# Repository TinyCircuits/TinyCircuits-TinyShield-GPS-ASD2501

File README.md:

# TinyCircuits TinyShield GPS Board
# ASD2501 Rev4

The design files are located under design_files/ for the TinyCircuits ASD2501 Rev 4 PCB.  This is a TinyShield board that has a GPS module, local power supply, antenna and level shifters to receive GPS data.

Format is in Cadsoft Eagle format - Eagle version 6.2 was used for the original design.

For more infomation on this, check out the product page at TinyCircuits.com:  https://tinycircuits.com/collections/sensors/products/gps-tinyshield

#License:

Design by TinyCircuits.
All design files are released under the Creative Commons Attribution Share-Alike 3.0 License, see the following link for details: http://creativecommons.org/licenses/by-sa/3.0

All text above must be included in any redistribution or derived design

This project uses designs and concepts developed as part of the Arduino project and the LilyPad project.  The TinyCircuits design files themselves (schematics, PCB and libraries) are not directly derived from these works' design files and have been created new, however the concepts and basic architecture behind the TinyDuino and TinyLily products are derived and we thank the hard work of the organizations below for their contributions to open-source hardware:
  
Original Arduino Uno Design by Team Arduino

LilyPad Arduino Design by Leah Buechley and Sparkfun Electronics

Please support the open-source hardware community

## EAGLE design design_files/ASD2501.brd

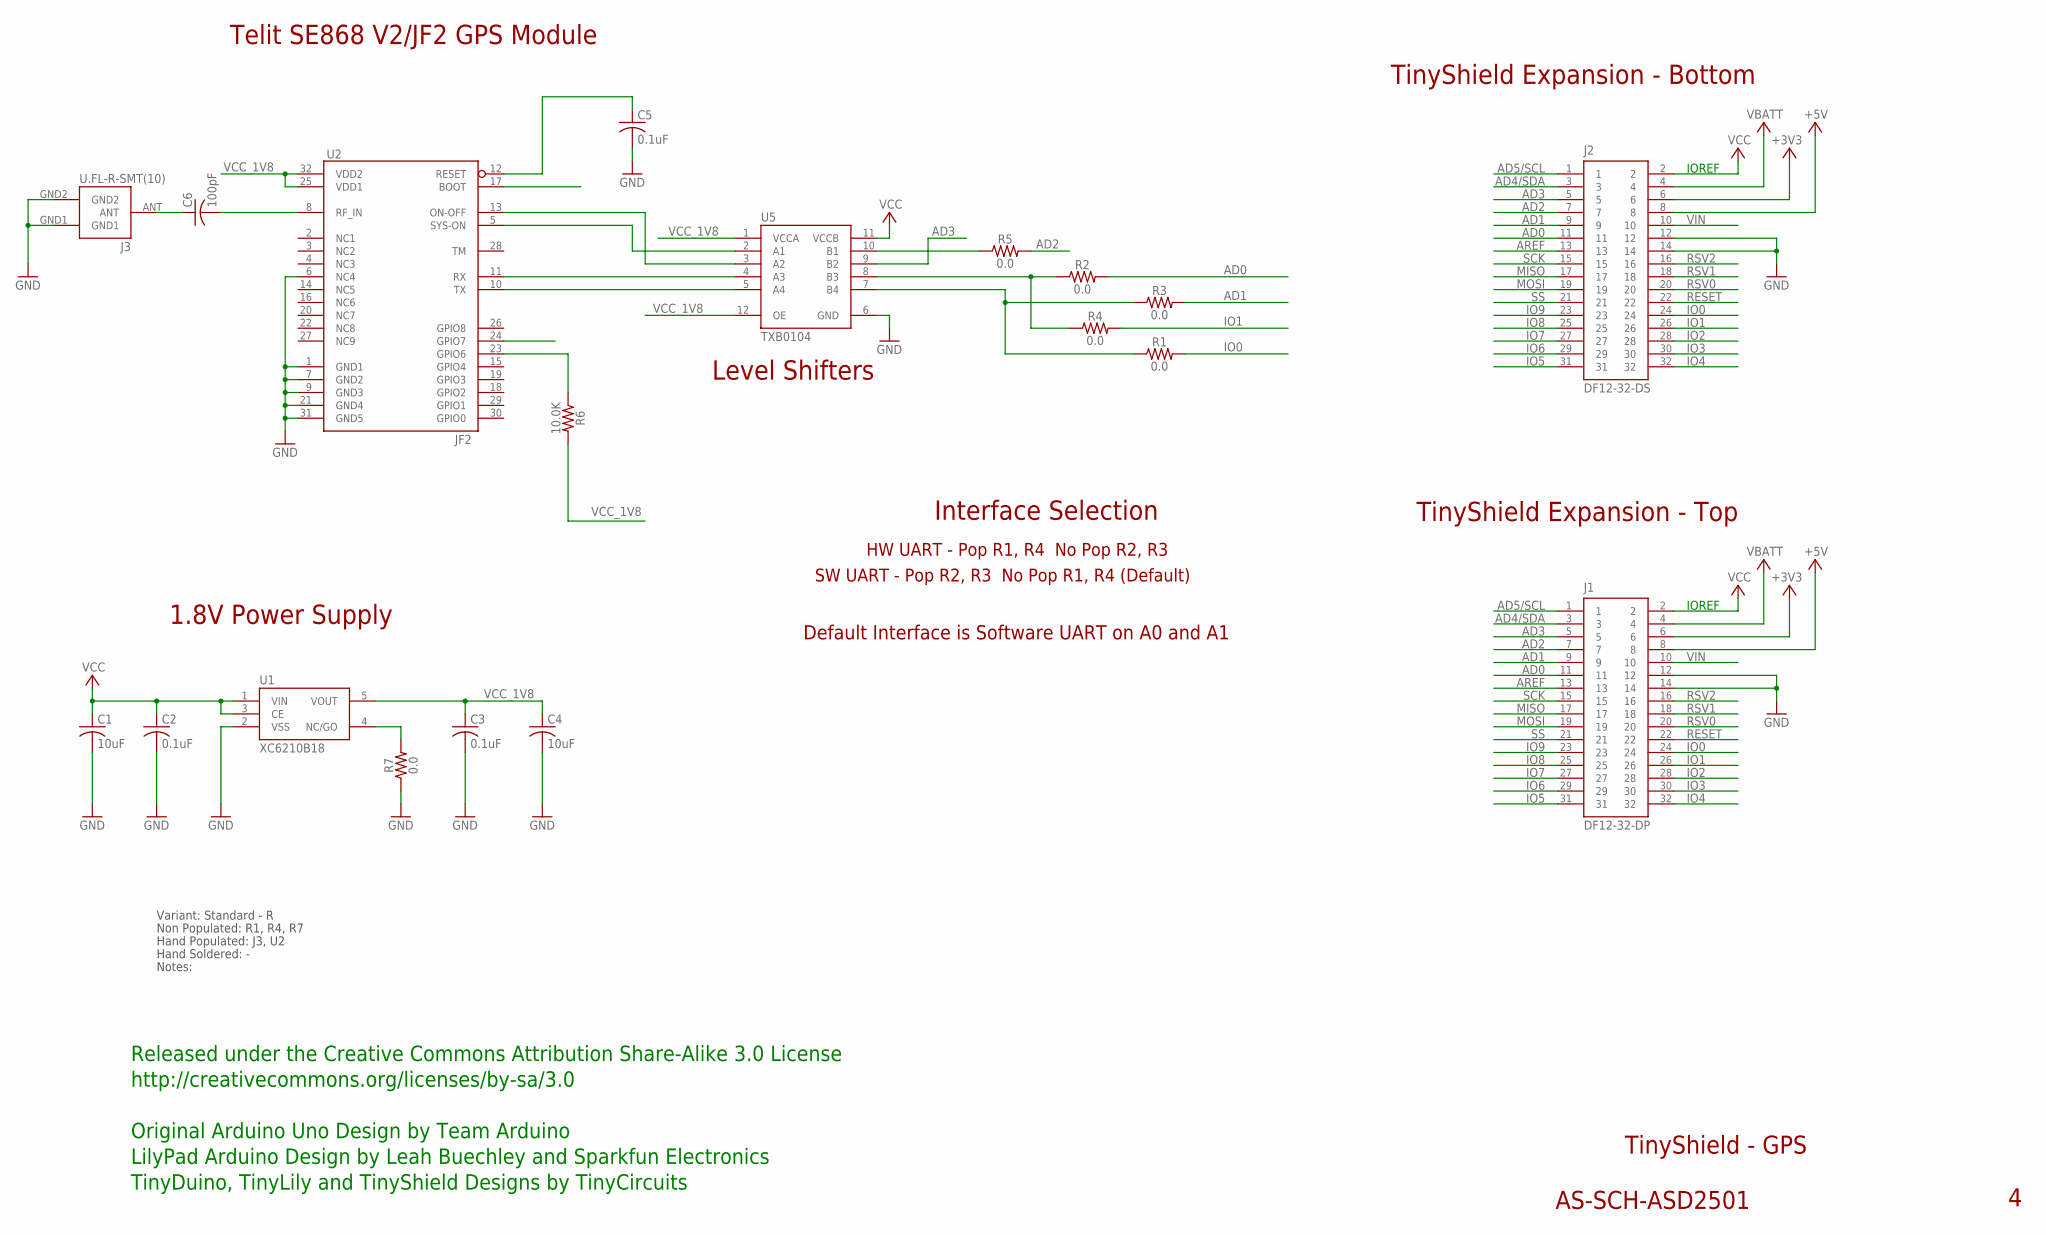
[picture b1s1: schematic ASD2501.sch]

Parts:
C1, C4: 10uF; C0805; PARTNO AS-ITM-00045
C2, C3, C5: 0.1uF; C0402; PARTNO AS-ITM-00008
C6: 100pF; 0402; PARTNO AS-ITM-00148
J1: DF12-32-DP; PARTNO AS-ITM-00015
J2: DF12-32-DS; PARTNO AS-ITM-00012
J3: U.FL-R-SMT(10)
R1, R2, R3, R4: 0.0; 0402
R5, R7: 0.0; 0402; PARTNO AS-ITM-00076
R6: 10.0K; 0402
U1: XC6210B18; SOT-25; PARTNO AS-ITM-00075
U2: JF2
U5: TXB0104; UQFN-12

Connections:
+3V3: J1.6, J2.6
+5V: J1.8, J2.8
AD0: J1.11, J2.11, R2.2
AD1: J1.9, J2.9, R3.2
AD2: J1.7, J2.7, R5.2
AD3: J1.5, J2.5, U5.9 (B2)
AD4/SDA: J1.3, J2.3
AD5/SCL: J1.1, J2.1
AREF: J1.13, J2.13
GND: C1.2, C2.2, C3.2, C4.2, C5.2, J1.12, J1.14, J2.12, J2.14, J3.GND1, J3.GND2, R7.1, U1.2 (VSS), U2.1 (GND1), U2.6 (NC4), U2.7 (GND2), U2.9 (GND3), U2.21 (GND4), U2.31 (GND5), U5.6 (GND)
IO0: J1.24, J2.24, R1.2
IO1: J1.26, J2.26, R4.2
IO2: J1.28, J2.28
IO3: J1.30, J2.30
IO4: J1.32, J2.32
IO5: J1.31, J2.31
IO6: J1.29, J2.29
IO7: J1.27, J2.27
IO8: J1.25, J2.25
IO9: J1.23, J2.23
MISO: J1.17, J2.17
MOSI: J1.19, J2.19
unnamed: C6.1, J3.ANT
unnamed: R2.1, R4.1, U5.8 (B3)
unnamed: R1.1, R3.1, U5.7 (B4)
unnamed: U2.11 (RX), U5.4 (A3)
unnamed: R6.1, U2.23 (GPIO6)
unnamed: R7.2, U1.4 (NC/GO)
unnamed: U2.10 (TX), U5.5 (A4)
unnamed: C5.1, U2.12 (RESET)
unnamed: C6.2, U2.8 (RF_IN)
unnamed: U2.13 (ON-OFF), U5.3 (A2)
unnamed: U2.5 (SYS-ON), U5.2 (A1)
unnamed: R5.1, U5.10 (B1)
RESET: J1.22, J2.22
RSV0: J1.20, J2.20
RSV1: J1.18, J2.18
RSV2: J1.16, J2.16
SCK: J1.15, J2.15
SS: J1.21, J2.21
VBATT: J1.4, J2.4
VCC: C1.1, C2.1, J1.2, J2.2, U1.1 (VIN), U1.3 (CE), U5.11 (VCCB)
VCC_1V8: C3.1, C4.1, R6.2, U1.5 (VOUT), U2.25 (VDD1), U2.32 (VDD2), U5.1 (VCCA), U5.12 (OE)
VIN: J1.10, J2.10

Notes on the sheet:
TinyShield Expansion - Bottom
TinyShield - GPS
AS-SCH-ASD2501
TinyShield Expansion - Top
IOREF
Released under the Creative Commons Attribution Share-Alike 3.0 License
http://creativecommons.org/licenses/by-sa/3.0
LilyPad Arduino Design by Leah Buechley and Sparkfun Electronics
TinyDuino, TinyLily and TinyShield Designs by TinyCircuits
Original Arduino Uno Design by Team Arduino
1.8V Power Supply
Telit SE868 V2/JF2 GPS Module
Level Shifters
Interface Selection
HW UART - Pop R1, R4 No Pop R2, R3
Default Interface is Software UART on A0 and A1
SW UART - Pop R2, R3 No Pop R1, R4 (Default)
Non Populated: R1, R4, R7
Hand Populated: J3, U2
Hand Soldered: -
Notes:
Variant: Standard - R

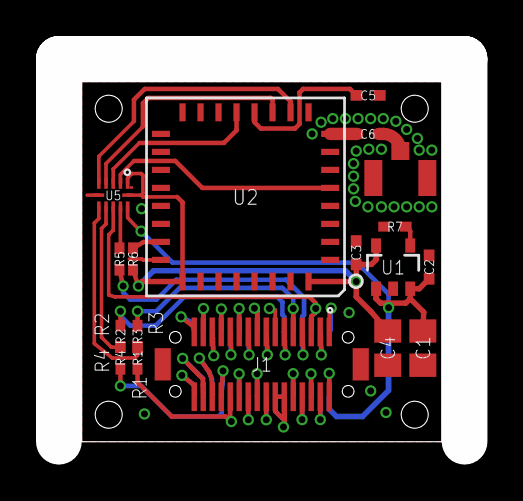
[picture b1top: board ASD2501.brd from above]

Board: 2 copper layers, 20.0 x 20.0 mm, 20 parts (1 on the bottom side), 44 nets.

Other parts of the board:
U$1: DOCFIELD-TINYCIRCUITS-PCB

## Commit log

2013-12-26 Updated antenna ref des
2014-08-24 Updated Link
2019-01-02 update format
2019-01-07 updated comments
2019-02-01 add images and examples
2019-03-15 update images
2019-05-22 added images
2019-05-23 updated images
2020-02-11 image update
2020-07-28 Add CAD data
2020-08-14 Update CAD drawing
